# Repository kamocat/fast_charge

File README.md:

# fast_charge
A flexible buck buck converter for fast charging cell phones from unreliable power sources

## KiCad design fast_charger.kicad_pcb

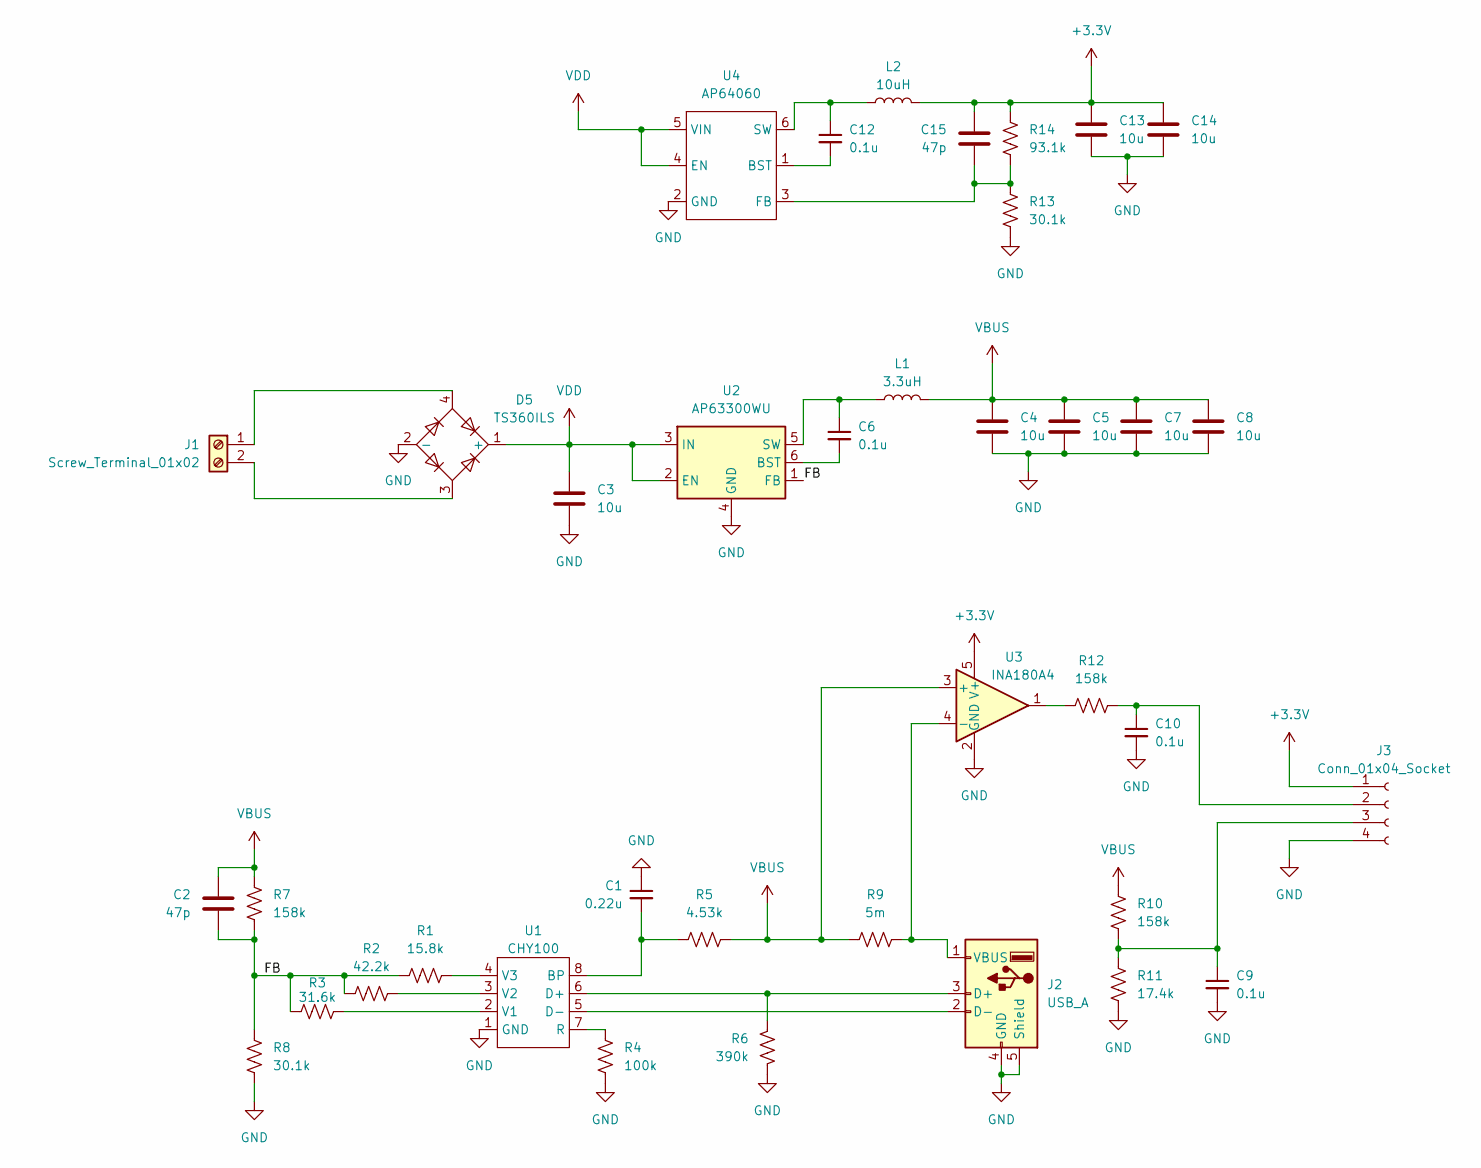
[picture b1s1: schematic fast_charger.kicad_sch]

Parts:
C1: 0.22u; C_0603_1608Metric
C2, C15: 47p; C_0603_1608Metric
C3, C4, C5, C7, C8: 10u; C_1206_3216Metric
C6, C9, C10, C12: 0.1u; C_0603_1608Metric
C13, C14: 10u; C_0805_2012Metric
D5: TS360ILS; TSSOP-4_4.4x5mm_P4mm
J1: Screw_Terminal_01x02; TerminalBlock_Phoenix_MKDS-3-2-5.08_1x02_P5.08mm_Horizontal
J2: USB_A; usb_CU01
J3: Conn_01x04_Socket; PinHeader_1x04_P2.54mm_Vertical
L1: 3.3uH; L_6.5x6.5
L2: 10uH; L_0805_2012Metric
R1: 15.8k; R_0603_1608Metric
R2: 42.2k; R_0603_1608Metric
R3: 31.6k; R_0603_1608Metric
R4: 100k; R_0603_1608Metric
R5: 4.53k; R_0603_1608Metric
R6: 390k; R_0603_1608Metric
R7, R10, R12: 158k; R_0603_1608Metric
R8, R13: 30.1k; R_0603_1608Metric
R9: 5m; R_0805_2012Metric
R11: 17.4k; R_0603_1608Metric
R14: 93.1k; R_0603_1608Metric
U1: CHY100; SO-8_3.9x4.9mm_P1.27mm
U2: AP63300WU; TSOT-23-6
U3: INA180A4; SOT-23-5
U4: AP64060; SOT-23-6

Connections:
+3.3V: C13.1, C14.1, C15.1, J3.1, L2.2, R14.1, U3.5 (V+)
/FB: C2.2, R1.1, R2.1, R3.1, R7.2, R8.1, U2.1 (FB)
GND: C1.1, C3.2, C4.2, C5.2, C7.2, C8.2, C9.2, C10.2, C13.2, C14.2, D5.2 (-), J2.4 (GND), J2.5 (Shield), J3.4, R4.2, R6.1, R8.2, R11.1, R13.2, U1.1 (GND), U2.4 (GND), U3.2 (GND), U4.2 (GND)
unnamed: D5.4, J1.1
unnamed: D5.3, J1.2
unnamed: J2.3 (D+), R6.2, U1.6 (D+)
unnamed: J2.2 (D-), U1.5 (D-)
unnamed: J2.1 (VBUS), R9.2, U3.4 (-)
unnamed: C10.1, J3.2, R12.2
unnamed: C9.1, J3.3, R10.2, R11.2
unnamed: R12.1, U3.1
unnamed: C1.2, R5.1, U1.8 (BP)
unnamed: R4.1, U1.7 (R)
unnamed: R3.2, U1.2 (V1)
unnamed: R2.2, U1.3 (V2)
unnamed: R1.2, U1.4 (V3)
unnamed: C6.2, U2.6 (BST)
unnamed: C6.1, L1.1, U2.5 (SW)
unnamed: C12.2, U4.1 (BST)
unnamed: C15.2, R13.1, R14.2, U4.3 (FB)
unnamed: C12.1, L2.1, U4.6 (SW)
VBUS: C2.1, C4.1, C5.1, C7.1, C8.1, L1.2, R5.2, R7.1, R9.1, R10.1, U3.3 (+)
VDD: C3.1, D5.1 (+), U2.2 (EN), U2.3 (IN), U4.4 (EN), U4.5 (VIN)

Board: 2 copper layers, 38 parts (0 on the bottom side), 23 nets, no tracks yet.

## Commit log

2023-11-05 initial schematic
2023-11-06 Completed BOM
2023-11-23 Completed placement
2023-11-25 Completed routing
2023-11-25 V1 complete. PCB and parts ordered
2023-12-18 MCU programming works
2023-12-19 Switched to AVR baremetal. PWM and ADC are working
2023-12-21 Regulates voltage ok.
    Burnt out PB2 so I'm using PB0 to drive the boost.
    I added 300 ohms inline to prevent burning out this output.
2023-12-26 Updated LEDs for more helpful indication
2023-12-26 Created simulation to improve control algorithm
2023-12-26 Added multi-rate charger. Instability comes out easily
2024-04-20 Too many issues. Moving to a simpler design
2024-04-20 New simpler buck-only design
    Bridge rectifier on input to allow reverse voltage
    Voltage regulation is taken care of by ASIC
    External microcontroller and OLED display show power/voltage/current
